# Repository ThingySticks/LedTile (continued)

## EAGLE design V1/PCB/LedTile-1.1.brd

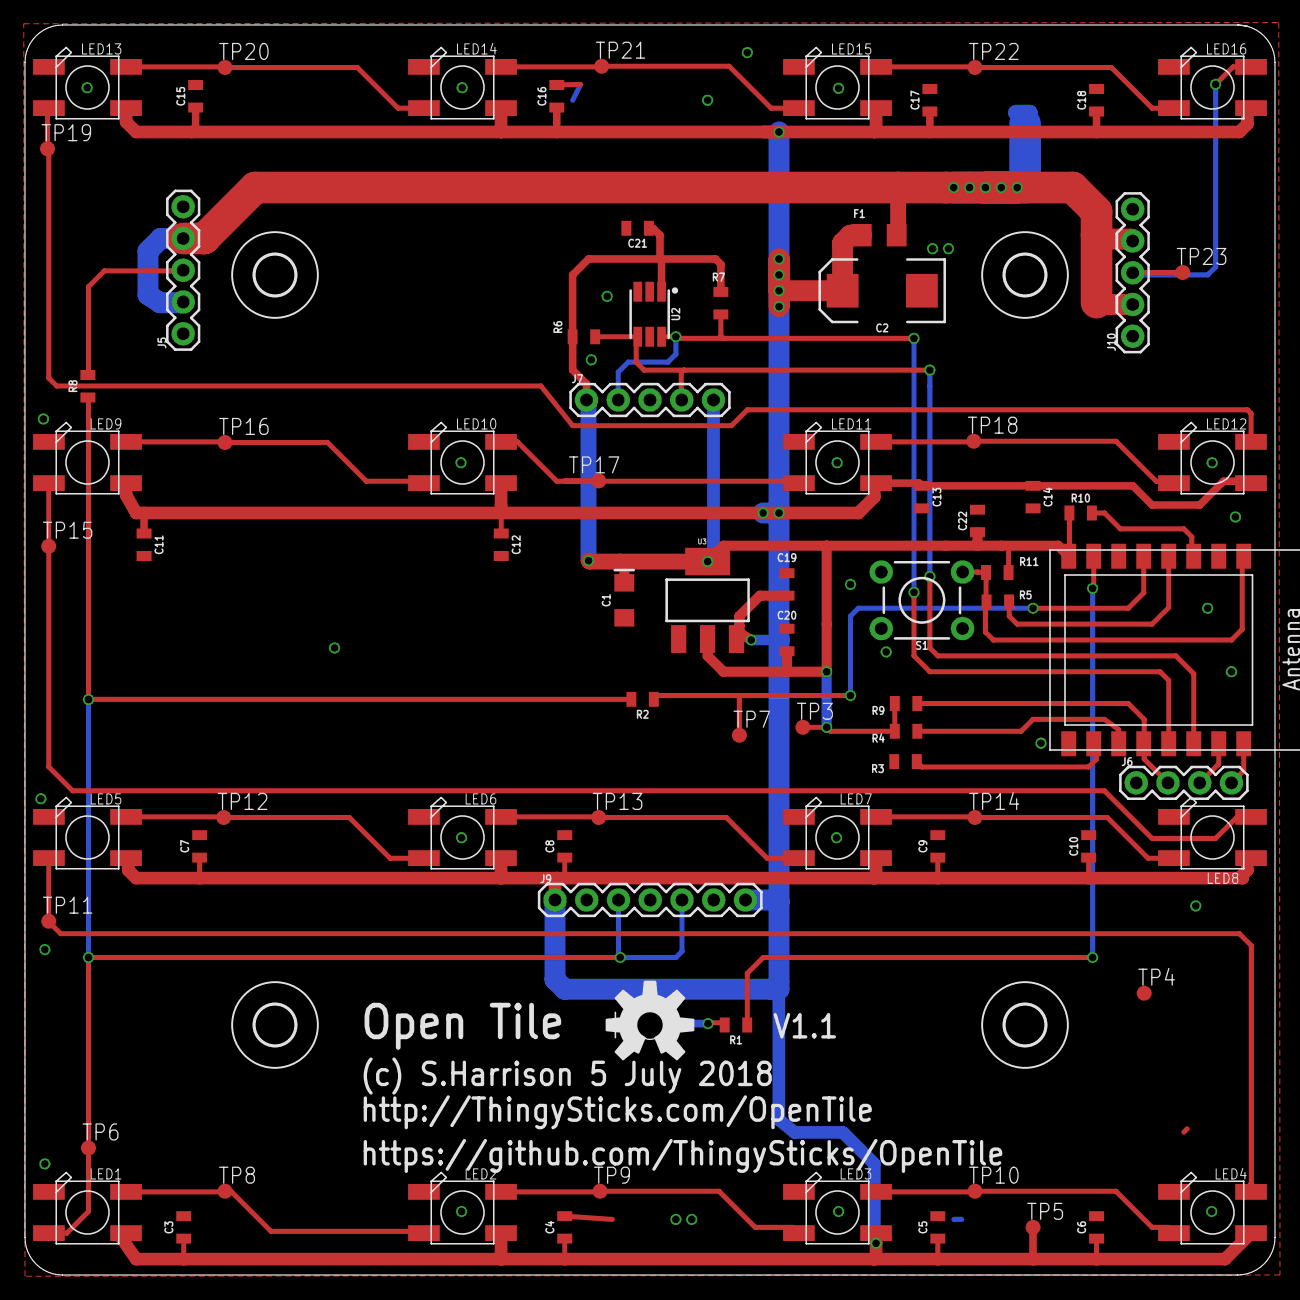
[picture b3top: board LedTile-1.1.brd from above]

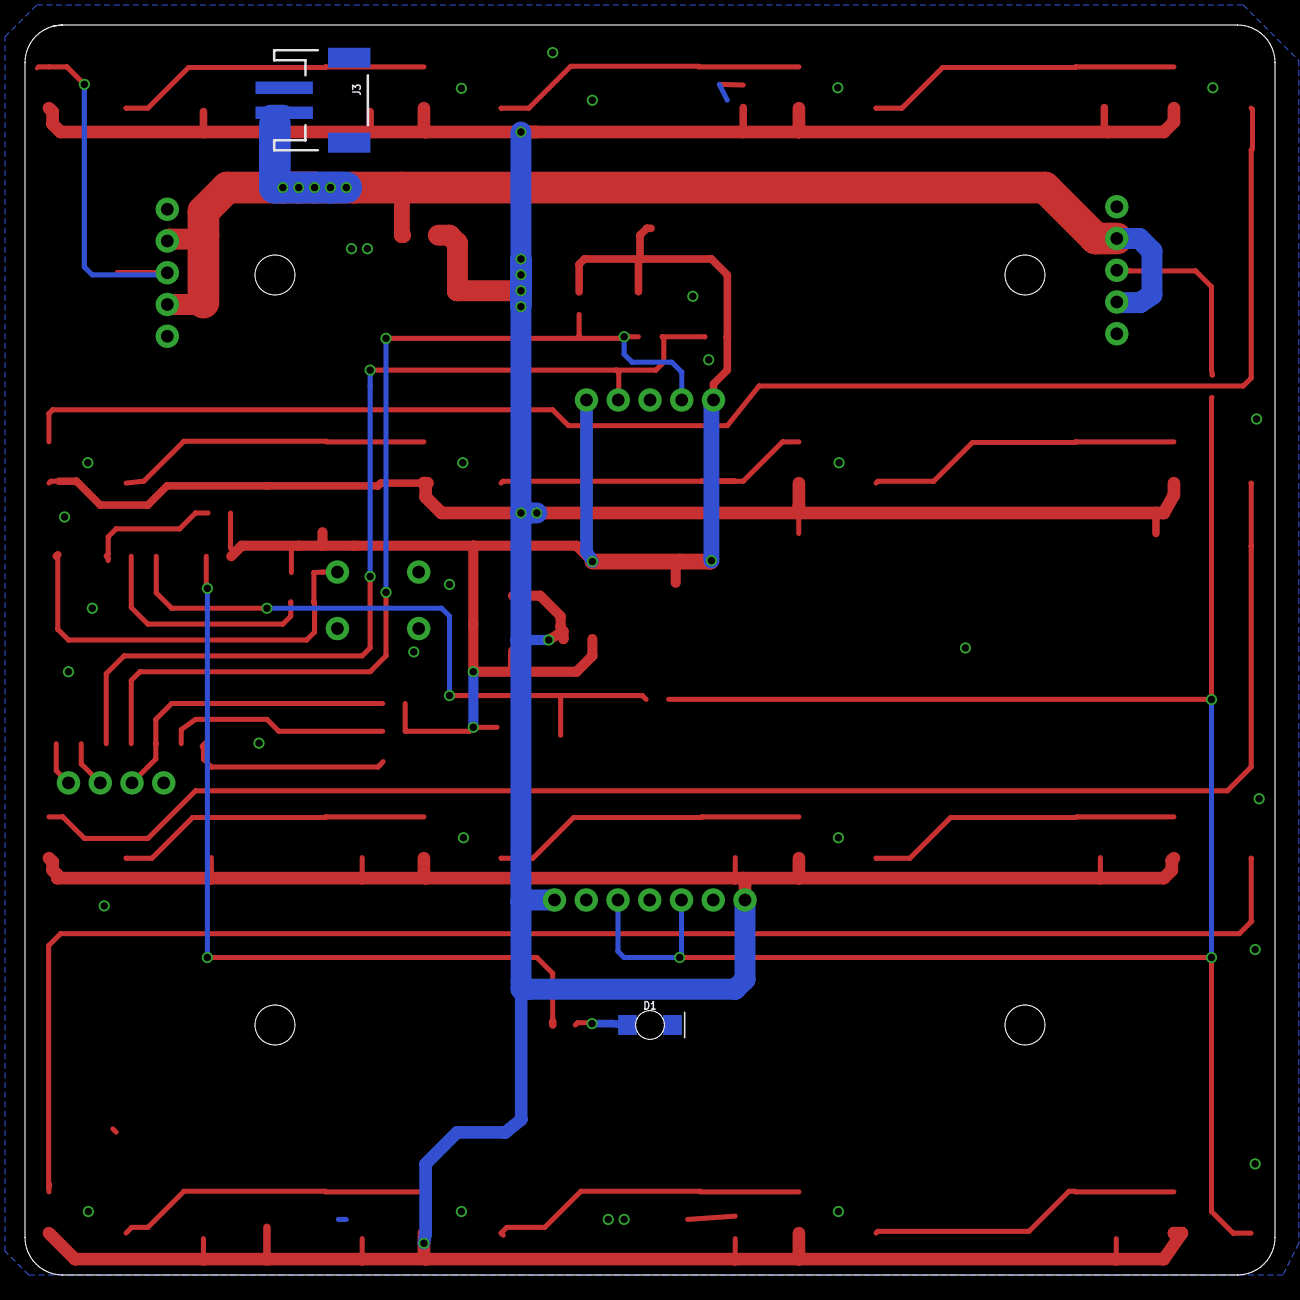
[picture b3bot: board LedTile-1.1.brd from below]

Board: 2 copper layers, 100.0 x 100.0 mm, 88 parts (2 on the bottom side), 35 nets.

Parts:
C1: 10uF; EIA3216
C2: 100uF; EIA7343
C3, C4, C5, C6, C7, C8, C9, C10, C11, C12, C13, C14, C15, C16, C17, C18, C19, C20: 1.0uF; 0805
C21, C22: 0.1uF; 0805
D1: LED-1206-BOTTOM
F1: 6V/0.75A; 1206
FRAME1: FRAME-LETTER; CREATIVE_COMMONS
H1, H2, H3, H4: MOUNT-HOLE3.2; 3,2
J3: JST-2-SMD
J5, J10: 1X05
J6: 1X04
J7: Compute Module; 1X05
J9: Compute Module; 1X07
LED1, LED2, LED3, LED4, LED5, LED6, LED7, LED8, LED9, LED10, LED11, LED12, LED13, LED14, LED15, LED16: WS2812BBIGPADS; WS2812B-BIGPADS
LOGO1: OSHW-LOGOL; OSHW-LOGO-L
R1, R5: 0805
R2, R8: 500R; 0805
R3: 1k; 0805
R4, R9, R10, R11: 10k; 0805
R6, R7: 4k7; 0805
S1: MOMENTARY-SWITCH-SPST-PTH-6.0MM; TACTILE_SWITCH_PTH_6.0MM
TP3, TP4, TP5, TP6, TP7, TP8, TP9, TP10, TP11, TP12, TP13, TP14, TP15, TP16, TP17, TP18, TP19, TP20, TP21, TP22, TP23: TPTP12R; TP12R
U2: TSL2561T; TMB-6
U3: SOT223
X1: ESP-12

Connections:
5V: C2.A, C3.1, C4.1, C5.1, C6.1, C7.1, C8.1, C9.1, C10.1, C11.1, C12.1, C13.1, C14.1, C15.1, C16.1, C17.1, C18.1, C19.1, F1.2, J9.1, J9.7, LED1.1-VDD, LED2.1-VDD, LED3.1-VDD, LED4.1-VDD, LED5.1-VDD, LED6.1-VDD, LED7.1-VDD, LED8.1-VDD, LED9.1-VDD, LED10.1-VDD, LED11.1-VDD, LED12.1-VDD, LED13.1-VDD, LED14.1-VDD, LED15.1-VDD, LED16.1-VDD, TP5.TP, U3.3
+3V3: C1.+, C20.1, C21.1, C22.1, J7.1, J7.5, R4.2, R6.2, R7.2, R9.2, R10.1, R11.2, TP3.TP, U2.1, U3.2, U3.4, X1.8
CH_PD: R10.2, X1.3
D0: J6.2, R9.1, X1.12
GND: C1.-, C2.C, C3.2, C4.2, C5.2, C6.2, C7.2, C8.2, C9.2, C10.2, C11.2, C12.2, C13.2, C14.2, C15.2, C16.2, C17.2, C18.2, C19.2, C20.2, C21.2, C22.2, D1.C, J3.1, J5.1, J5.5, J6.1, J7.3, J9.2, J9.4, J9.6, J10.1, J10.5, LED1.3-GND, LED2.3-GND, LED3.3-GND, LED4.3-GND, LED5.3-GND, LED6.3-GND, LED7.3-GND, LED8.3-GND, LED9.3-GND, LED10.3-GND, LED11.3-GND, LED12.3-GND, LED13.3-GND, LED14.3-GND, LED15.3-GND, LED16.3-GND, R3.2, S1.1, TP4.TP, U2.2, U2.3, U3.1, X1.9
LEDS_DATA: R2.1, TP7.TP, X1.5
LEDS_DIN: J9.3, J9.5, LED1.4-DIN, R2.2, R8.1, TP6.TP
LEDS_DOUT: J10.3, LED16.2-DOUT, TP23.TP
unnamed: LED1.2-DOUT, LED2.4-DIN, TP8.TP
unnamed: J5.3, R8.2
unnamed: R3.1, X1.10
unnamed: R4.1, X1.11
unnamed: LED2.2-DOUT, LED3.4-DIN, TP9.TP
unnamed: LED3.2-DOUT, LED4.4-DIN, TP10.TP
unnamed: LED4.2-DOUT, LED5.4-DIN, TP11.TP
unnamed: R5.2, X1.4
unnamed: D1.A, R1.2
unnamed: LED8.2-DOUT, LED9.4-DIN, TP15.TP
unnamed: LED12.2-DOUT, LED13.4-DIN, TP19.TP
unnamed: LED5.2-DOUT, LED6.4-DIN, TP12.TP
unnamed: LED6.2-DOUT, LED7.4-DIN, TP13.TP
unnamed: LED7.2-DOUT, LED8.4-DIN, TP14.TP
unnamed: LED9.2-DOUT, LED10.4-DIN, TP16.TP
unnamed: LED10.2-DOUT, LED11.4-DIN, TP17.TP
unnamed: LED11.2-DOUT, LED12.4-DIN, TP18.TP
unnamed: LED13.2-DOUT, LED14.4-DIN, TP20.TP
unnamed: LED14.2-DOUT, LED15.4-DIN, TP21.TP
unnamed: LED15.2-DOUT, LED16.4-DIN, TP22.TP
OSH_LED: R1.1, X1.7
RESET: R5.1, R11.1, S1.3, X1.1
RX: J6.3, X1.15
SCL: J7.4, R6.1, U2.4, X1.14
SDA: J7.2, R7.1, U2.6, X1.13
TX: J6.4, X1.16
VIN: F1.1, J3.2, J5.2, J5.4, J10.2, J10.4

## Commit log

2018-06-04 Initial version as sent to DirtyPCBs
2018-06-07 Added dimensions.
2018-06-07 Adding initial ideas for enclosure.
2018-06-07 Start of a larger tile
2018-06-15 Added V1 schematic
2018-07-06 V1.1 as sent to DirtyPCBs.
    Added pullups required for ESP-12E
    Added reset button option
    Modified LED footprints to give a bigger area for soldering
    Changed connectors for tile2tile to 5 pin SIL with reversable connections.
    Added "compute board" pin headers to allow a behing board to have ESP on in future designs.
2018-07-06 Improvements to fitting of the lid.
    Updating for options for 180mm tile.
2018-07-06 Individual LED difuser.
